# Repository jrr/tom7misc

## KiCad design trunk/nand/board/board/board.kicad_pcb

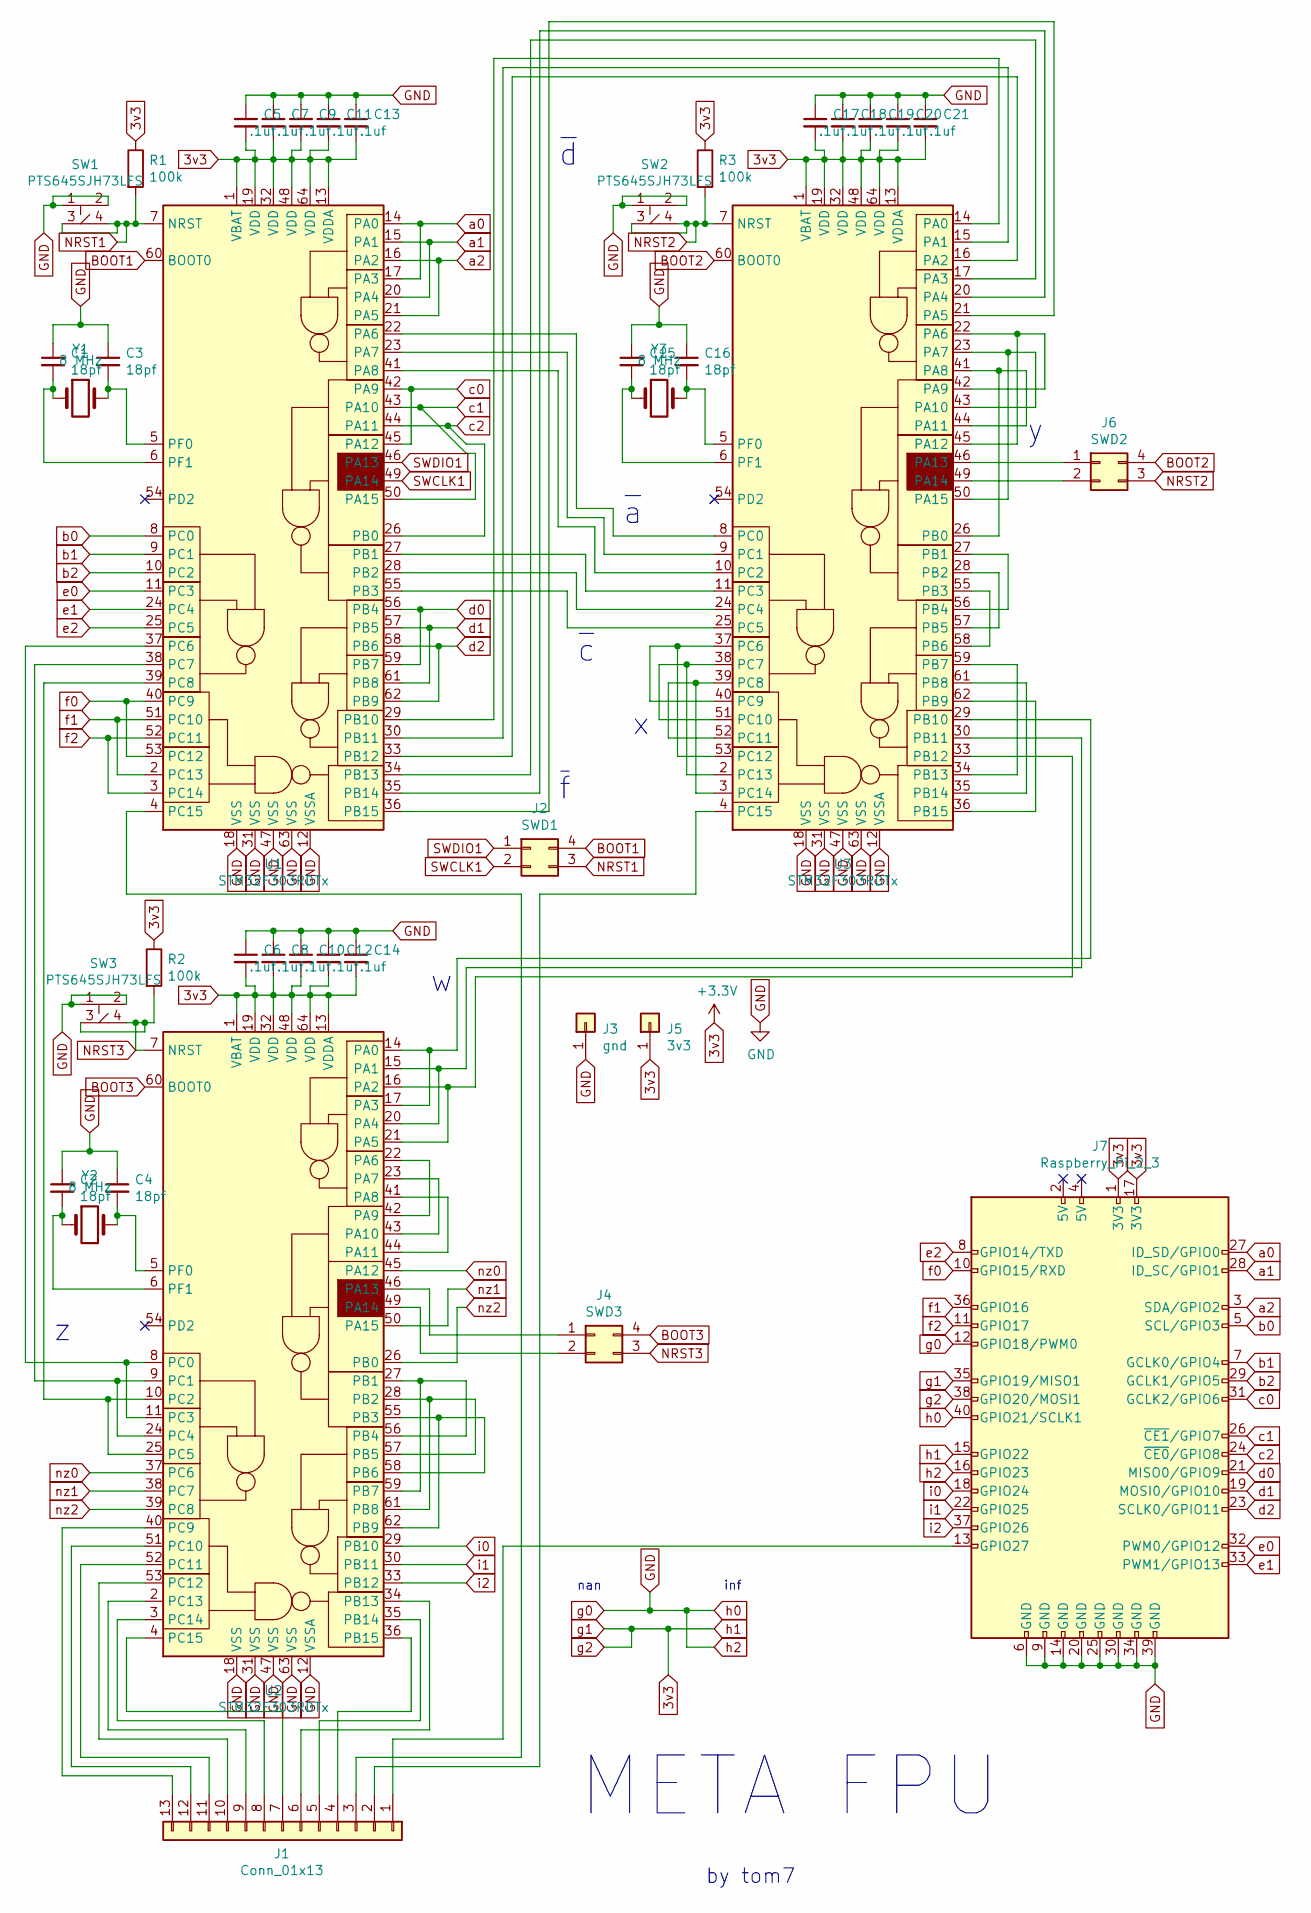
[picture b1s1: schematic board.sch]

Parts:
C1, C2, C3, C4, C15, C16: 18pf; C_Disc_D6.0mm_W2.5mm_P5.00mm
C5, C6, C7, C8, C9, C10, C11, C12, C13, C14, C17, C18, C19, C20, C21: .1uf; C_Disc_D6.0mm_W2.5mm_P5.00mm
J1: Conn_01x13; PinHeader_1x13_P2.54mm_Vertical
J2: SWD1; PinHeader_2x02_P2.54mm_Vertical
J3: gnd; PinHeader_1x01_P2.54mm_Vertical
J4: SWD3; PinHeader_2x02_P2.54mm_Vertical
J5: 3v3; PinHeader_1x01_P2.54mm_Vertical
J6: SWD2; PinHeader_2x02_P2.54mm_Vertical
J7: Raspberry_Pi_2_3; PinHeader_2x20_P2.54mm_Vertical
R1, R2, R3: 100k; R_Axial_DIN0207_L6.3mm_D2.5mm_P7.62mm_Horizontal
SW1, SW2, SW3: PTS645SJH73LFS; PTS645SJH73LFS_FP
U1, U2, U3: STM32F303RDTx; LQFP-64_10x10mm_P0.5mm
Y1, Y2, Y3: 8 MHz; Crystal_HC49-U_Vertical

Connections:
3v3: C5.2, C6.2, C7.2, C8.2, C9.2, C10.2, C11.2, C12.2, C13.2, C14.2, C17.2, C18.2, C19.2, C20.2, C21.2, J5.1, J7.1 (3V3), J7.15 (GPIO22), J7.17 (3V3), J7.35 (GPIO19/MISO1), J7.38 (GPIO20/MOSI1), R1.1, R2.1, R3.1, U1.1 (VBAT), U1.13 (VDDA), U1.19 (VDD), U1.32 (VDD), U1.48 (VDD), U1.64 (VDD), U2.1 (VBAT), U2.13 (VDDA), U2.19 (VDD), U2.32 (VDD), U2.48 (VDD), U2.64 (VDD), U3.1 (VBAT), U3.13 (VDDA), U3.19 (VDD), U3.32 (VDD), U3.48 (VDD), U3.64 (VDD)
BOOT1: J2.4, U1.60 (BOOT0)
BOOT2: J6.4, U3.60 (BOOT0)
BOOT3: J4.4, U2.60 (BOOT0)
GND: C1.1, C2.1, C3.1, C4.1, C5.1, C6.1, C7.1, C8.1, C9.1, C10.1, C11.1, C12.1, C13.1, C14.1, C15.1, C16.1, C17.1, C18.1, C19.1, C20.1, C21.1, J3.1, J7.6 (GND), J7.9 (GND), J7.12 (GPIO18/PWM0), J7.14 (GND), J7.16 (GPIO23), J7.20 (GND), J7.25 (GND), J7.30 (GND), J7.34 (GND), J7.39 (GND), J7.40 (GPIO21/SCLK1), SW1.1, SW1.2, SW2.1, SW2.2, SW3.1, SW3.2, U1.12 (VSSA), U1.18 (VSS), U1.31 (VSS), U1.47 (VSS), U1.63 (VSS), U2.12 (VSSA), U2.18 (VSS), U2.31 (VSS), U2.47 (VSS), U2.63 (VSS), U3.12 (VSSA), U3.18 (VSS), U3.31 (VSS), U3.47 (VSS), U3.63 (VSS)
NRST1: J2.3, R1.2, SW1.3, SW1.4, U1.7 (NRST)
NRST2: J6.3, R3.2, SW2.3, SW2.4, U3.7 (NRST)
NRST3: J4.3, R2.2, SW3.3, SW3.4, U2.7 (NRST)
unnamed: C1.2, U1.6 (PF1), Y1.1
unnamed: C2.2, U2.6 (PF1), Y2.1
unnamed: C3.2, U1.5 (PF0), Y1.2
unnamed: C4.2, U2.5 (PF0), Y2.2
unnamed: C15.2, U3.6 (PF1), Y3.1
unnamed: C16.2, U3.5 (PF0), Y3.2
unnamed: J1.1, J7.13 (GPIO27)
unnamed: J1.2, U3.4 (PC15)
unnamed: J1.3, U1.4 (PC15)
unnamed: J1.4, U2.36 (PB15)
unnamed: J1.5, U2.35 (PB14)
unnamed: J1.6, U2.34 (PB13)
unnamed: J1.7, U2.4 (PC15)
unnamed: J1.8, U2.3 (PC14)
unnamed: J1.9, U2.2 (PC13)
unnamed: J1.10, U2.53 (PC12)
unnamed: J1.11, U2.52 (PC11)
unnamed: J1.12, U2.51 (PC10)
unnamed: J1.13, U2.40 (PC9)
unnamed: J4.1, U2.46 (PA13)
unnamed: J4.2, U2.49 (PA14)
unnamed: J6.1, U3.46 (PA13)
unnamed: J6.2, U3.49 (PA14)
unnamed: U1.22 (PA6), U3.8 (PC0)
unnamed: U1.23 (PA7), U3.9 (PC1)
unnamed: U1.27 (PB1), U3.11 (PC3)
unnamed: U1.28 (PB2), U3.24 (PC4)
unnamed: U1.29 (PB10), U3.14 (PA0)
unnamed: U1.30 (PB11), U3.15 (PA1)
unnamed: U1.33 (PB12), U3.16 (PA2)
unnamed: U1.34 (PB13), U3.17 (PA3)
unnamed: U1.35 (PB14), U3.20 (PA4)
unnamed: U1.36 (PB15), U3.21 (PA5)
unnamed: U1.37 (PC6), U2.8 (PC0), U2.11 (PC3)
unnamed: U1.38 (PC7), U2.9 (PC1), U2.24 (PC4)
unnamed: U1.39 (PC8), U2.10 (PC2), U2.25 (PC5)
unnamed: U1.41 (PA8), U3.10 (PC2)
unnamed: U1.55 (PB3), U3.25 (PC5)
unnamed: U2.14 (PA0), U2.17 (PA3), U3.29 (PB10)
unnamed: U2.15 (PA1), U2.20 (PA4), U3.30 (PB11)
unnamed: U2.16 (PA2), U2.21 (PA5), U3.33 (PB12)
unnamed: U2.22 (PA6), U2.42 (PA9)
unnamed: U2.23 (PA7), U2.43 (PA10)
unnamed: U2.27 (PB1), U2.56 (PB4), U2.59 (PB7)
unnamed: U2.28 (PB2), U2.57 (PB5), U2.61 (PB8)
unnamed: U2.41 (PA8), U2.44 (PA11)
unnamed: U2.55 (PB3), U2.58 (PB6), U2.62 (PB9)
unnamed: U3.2 (PC13), U3.38 (PC7), U3.51 (PC10)
unnamed: U3.3 (PC14), U3.39 (PC8), U3.52 (PC11)
unnamed: U3.22 (PA6), U3.42 (PA9), U3.45 (PA12)
unnamed: U3.23 (PA7), U3.43 (PA10), U3.50 (PA15)
unnamed: U3.26 (PB0), U3.41 (PA8), U3.44 (PA11)
unnamed: U3.27 (PB1), U3.56 (PB4)
unnamed: U3.28 (PB2), U3.57 (PB5)
unnamed: U3.34 (PB13), U3.59 (PB7)
unnamed: U3.35 (PB14), U3.61 (PB8)
unnamed: U3.36 (PB15), U3.62 (PB9)
unnamed: U3.37 (PC6), U3.40 (PC9), U3.53 (PC12)
unnamed: U3.55 (PB3), U3.58 (PB6)
SWCLK1: J2.2, U1.49 (PA14)
SWDIO1: J2.1, U1.46 (PA13)
a0: J7.27 (ID_SD/GPIO0), U1.14 (PA0), U1.17 (PA3)
a1: J7.28 (ID_SC/GPIO1), U1.15 (PA1), U1.20 (PA4)
a2: J7.3 (SDA/GPIO2), U1.16 (PA2), U1.21 (PA5)
b0: J7.5 (SCL/GPIO3), U1.8 (PC0)
b1: J7.7 (GCLK0/GPIO4), U1.9 (PC1)
b2: J7.29 (GCLK1/GPIO5), U1.10 (PC2)
c0: J7.31 (GCLK2/GPIO6), U1.42 (PA9), U1.45 (PA12)
c1: J7.26 (~CE1~/GPIO7), U1.43 (PA10), U1.50 (PA15)
c2: J7.24 (~CE0~/GPIO8), U1.26 (PB0), U1.44 (PA11)
d0: J7.21 (MISO0/GPIO9), U1.56 (PB4), U1.59 (PB7)
d1: J7.19 (MOSI0/GPIO10), U1.57 (PB5), U1.61 (PB8)
d2: J7.23 (SCLK0/GPIO11), U1.58 (PB6), U1.62 (PB9)
e0: J7.32 (PWM0/GPIO12), U1.11 (PC3)
e1: J7.33 (PWM1/GPIO13), U1.24 (PC4)
e2: J7.8 (GPIO14/TXD), U1.25 (PC5)
f0: J7.10 (GPIO15/RXD), U1.40 (PC9), U1.53 (PC12)
f1: J7.36 (GPIO16), U1.2 (PC13), U1.51 (PC10)
f2: J7.11 (GPIO17), U1.3 (PC14), U1.52 (PC11)
i0: J7.18 (GPIO24), U2.29 (PB10)
i1: J7.22 (GPIO25), U2.30 (PB11)
i2: J7.37 (GPIO26), U2.33 (PB12)
nz0: U2.37 (PC6), U2.45 (PA12)
nz1: U2.38 (PC7), U2.50 (PA15)
nz2: U2.26 (PB0), U2.39 (PC8)

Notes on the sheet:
META FPU
by tom7
nan
inf

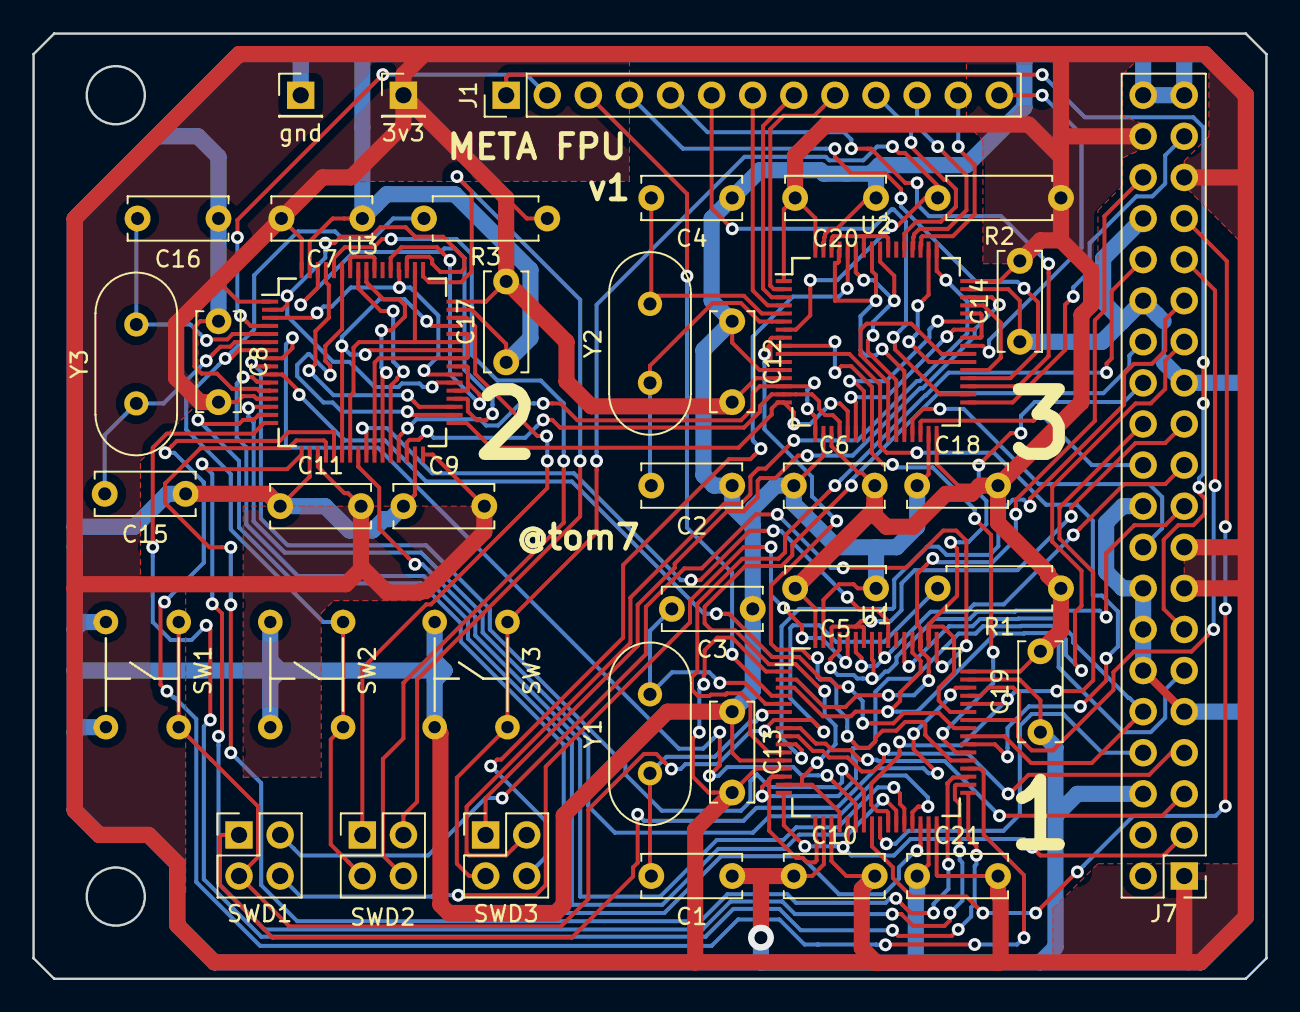
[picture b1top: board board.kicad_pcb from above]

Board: 2 copper layers, 76.2 x 58.4 mm, 40 parts (0 on the bottom side), 93 nets.

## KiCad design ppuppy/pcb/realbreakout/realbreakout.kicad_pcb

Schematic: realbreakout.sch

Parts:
.1uf1, .1uf2, .1uf3: C; C_Disc_D5.0mm_W2.5mm_P5.00mm
E1: GLS29EE010; DIP-32_W15.24mm
J1, J2, J3: Conn_01x36; Pin_Header_Straight_1x36_Pitch2.54mm
J4: BCM25; Pin_Header_Straight_1x01_Pitch2.54mm
J5: BCM24; Pin_Header_Straight_1x01_Pitch2.54mm
J6: BCM27; Pin_Header_Straight_1x01_Pitch2.54mm
J7: 3V; Pin_Header_Straight_1x01_Pitch2.54mm
J8: GND; Pin_Header_Straight_1x01_Pitch2.54mm
J9: BCM10; Pin_Header_Straight_1x01_Pitch2.54mm
J10: BCM11; Pin_Header_Straight_1x01_Pitch2.54mm
J11: BCM13; Pin_Header_Straight_1x01_Pitch2.54mm
J12: /OE; Pin_Header_Straight_1x01_Pitch2.54mm
U1: nescartheader; cartedge
U2: piheader; Pin_Header_Straight_2x20_Pitch2.54mm
U3: nescic; DIP-16_W7.62mm
U4: CD74FCT245; DIP-20_W7.62mm
U5, U6: MC74VHCT50A; SOIC-14_3.9x8.7mm_Pitch1.27mm

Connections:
3v: .1uf2.2, .1uf3.2, J7.1, U2.1 (3v3), U2.17 (3v3), U5.14 (VCC), U6.14 (VCC)
3vA0: U2.8 (BCM14_TXD), U6.2 (Y1)
3vA1: U2.10 (BCM15_RXD), U6.4 (Y2)
3vA2: U2.36 (BCM16), U6.6 (Y3)
3vA3: U2.11 (BCM17), U6.8 (Y4)
3vA4: U2.12 (BCM18_PWM0), U6.10 (Y5)
3vA5: U2.35 (BCM19_MISO), U6.12 (Y6)
3vA6: U2.38 (BCM20_MOSI), U5.2 (Y1)
3vA7: U2.40 (BCM21_SCLK), U5.4 (Y2)
3vA8: U2.15 (BCM22), U5.6 (Y3)
3vA9: U2.16 (BCM23), U5.8 (Y4)
3vA13: U2.37 (BCM26), U5.10 (Y5)
3vRD: J12.1, U2.32 (BCM12_PWM0), U4.19 (/OE), U5.12 (Y6)
/5vRD: J1.21, U1.21 (/PPU_RD), U5.13 (A6)
/ROMSEL: E1.24 (/OE), J2.23, J3.23, U1.50 (/ROMSEL)
unnamed: E1.4 (A12), J2.34, J3.34, U1.39 (CPU_A12)
unnamed: E1.5 (A7), J1.6, U1.6 (CPU_A7)
unnamed: E1.6 (A6), J1.7, U1.7 (CPU_A6)
unnamed: E1.7 (A5), J1.8, U1.8 (CPU_A5)
unnamed: E1.8 (A4), J1.9, U1.9 (CPU_A4)
unnamed: E1.9 (A3), J1.10, U1.10 (CPU_A3)
unnamed: E1.10 (A2), J1.11, U1.11 (CPU_A2)
unnamed: E1.11 (A1), J1.12, U1.12 (CPU_A1)
unnamed: E1.12 (A0), J1.13, U1.13 (CPU_A0)
unnamed: E1.13 (D0), J2.24, J3.24, U1.49 (CPU_D0)
unnamed: E1.14 (D1), J2.25, J3.25, U1.48 (CPU_D1)
unnamed: E1.15 (D2), J2.26, J3.26, U1.47 (CPU_D2)
unnamed: E1.17 (D3), J2.27, J3.27, U1.46 (CPU_D3)
unnamed: E1.18 (D4), J2.28, J3.28, U1.45 (CPU_D4)
unnamed: E1.19 (D5), J2.29, J3.29, U1.44 (CPU_D5)
unnamed: E1.20 (D6), J2.30, J3.30, U1.43 (CPU_D6)
unnamed: E1.21 (D7), J2.31, J3.31, U1.42 (CPU_D7)
unnamed: E1.23 (A10), J1.3, U1.3 (CPU_A10)
unnamed: E1.25 (A11), J1.2, U1.2 (CPU_A11)
unnamed: E1.26 (A9), J1.4, U1.4 (CPU_A9)
unnamed: E1.27 (A8), J1.5, U1.5 (CPU_A8)
unnamed: E1.28 (A13), J2.33, J3.33, U1.40 (CPU_A13)
unnamed: E1.29 (A14), J2.32, J3.32, U1.41 (CPU_A14)
unnamed: J1.14, U1.14 (CPU_R/W)
unnamed: J1.15, U1.15 (/IRQ)
unnamed: J1.16, U1.16 (EXP_0)
unnamed: J1.17, U1.17 (EXP_1)
unnamed: J1.18, U1.18 (EXP_2)
unnamed: J1.19, U1.19 (EXP_3)
unnamed: J1.20, U1.20 (EXP_4)
unnamed: J1.22, U1.22 (CIRAM_A10)
unnamed: J1.23, U1.23 (PPU_A6), U5.1 (A1)
unnamed: J1.24, U1.24 (PPU_A5), U6.13 (A6)
unnamed: J1.25, U1.25 (PPU_A4), U6.11 (A5)
unnamed: J1.26, U1.26 (PPU_A3), U6.9 (A4)
unnamed: J1.27, U1.27 (PPU_A2), U6.5 (A3)
unnamed: J1.28, U1.28 (PPU_A1), U6.3 (A2)
unnamed: J1.29, U1.29 (PPU_A0), U6.1 (A1)
unnamed: J1.30, U1.30 (PPU_D0), U4.9 (A8)
unnamed: J1.31, U1.31 (PPU_D1), U4.8 (A7)
unnamed: J1.32, U1.32 (PPU_D2), U4.7 (A6)
unnamed: J1.33, U1.33 (PPU_D3), U4.6 (A5)
unnamed: J1.34, U1.34 (CIC_toPak), U3.2 (DATA_IN)
unnamed: J1.35, U1.35 (CIC_toMB), U3.1 (DATA_OUT)
unnamed: J2.2, J3.2, U1.71 (CIC_CLK), U3.6 (CLK)
unnamed: J2.3, J3.3, U1.70 (/CIC_RST), U3.7 (RESET)
unnamed: J2.4, J3.4, U1.69 (PPU_D4), U4.5 (A4)
unnamed: J2.5, J3.5, U1.68 (PPU_D5), U4.4 (A3)
unnamed: J2.6, J3.6, U1.67 (PPU_D6), U4.3 (A2)
unnamed: J2.7, J3.7, U1.66 (PPU_D7), U4.2 (A1)
unnamed: J2.8, J3.8, U1.65 (PPU_A13), U5.11 (A5)
unnamed: J2.9, J3.9, U1.64 (PPU_A12)
unnamed: J2.10, J3.10, U1.63 (PPU_A10)
unnamed: J2.11, J3.11, U1.62 (PPU_A11)
unnamed: J2.12, J3.12, U1.61 (PPU_A9), U5.9 (A4)
unnamed: J2.13, J3.13, U1.60 (PPU_A8), U5.5 (A3)
unnamed: J2.14, J3.14, U1.59 (PPU_A7), U5.3 (A2)
unnamed: J2.15, J3.15, U1.58 (/PPU_A13)
unnamed: J2.17, J3.17, U1.56 (/PPU_WR)
unnamed: J2.18, J3.18, U1.55 (EXP_5)
unnamed: J2.19, J3.19, U1.54 (EXP_6)
unnamed: J2.20, J3.20, U1.53 (EXP_7)
unnamed: J2.21, J3.21, U1.52 (EXP_8)
unnamed: J2.22, J3.22, U1.51 (EXP_9)
unnamed: J2.35, J3.35, U1.38 (M2)
unnamed: J2.36, J3.36, U1.37 (SYS_CLK)
unnamed: J4.1, U2.22 (BCM25)
unnamed: J5.1, U2.18 (BCM24)
unnamed: J6.1, U2.13 (BCM27)
unnamed: J9.1, U2.19 (BCM10_MOSI)
unnamed: J10.1, U2.23 (BCM11_SCLK)
unnamed: J11.1, U2.33 (BCM13_PWM1)
unnamed: U2.3 (BCM2), U4.18 (B1)
unnamed: U2.5 (BCM3_SCL), U4.17 (B2)
unnamed: U2.7 (BCM4_CLK0), U4.16 (B3)
unnamed: U2.21 (BCM9_MISO), U4.11 (B8)
unnamed: U2.24 (BCM8_CE0), U4.12 (B7)
unnamed: U2.26 (BCM7_CE1), U4.13 (B6)
unnamed: U2.29 (BCM5), U4.15 (B4)
unnamed: U2.31 (BCM6), U4.14 (B5)

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
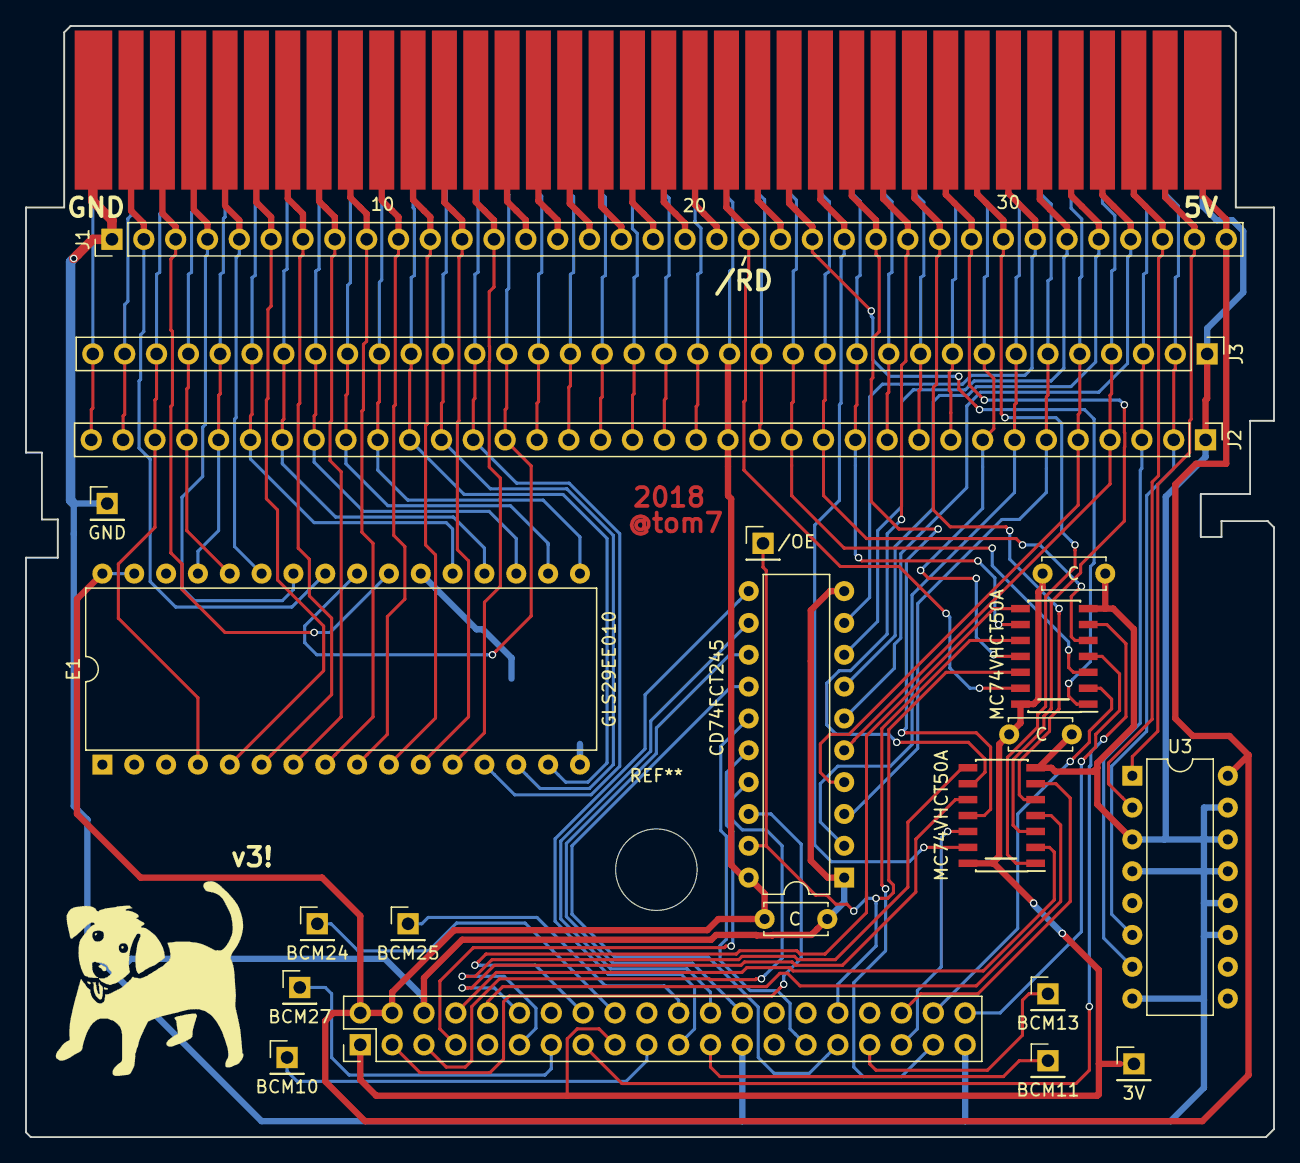
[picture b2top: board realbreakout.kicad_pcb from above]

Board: 2 copper layers, 99.6 x 88.6 mm, 22 parts (0 on the bottom side), 97 nets.

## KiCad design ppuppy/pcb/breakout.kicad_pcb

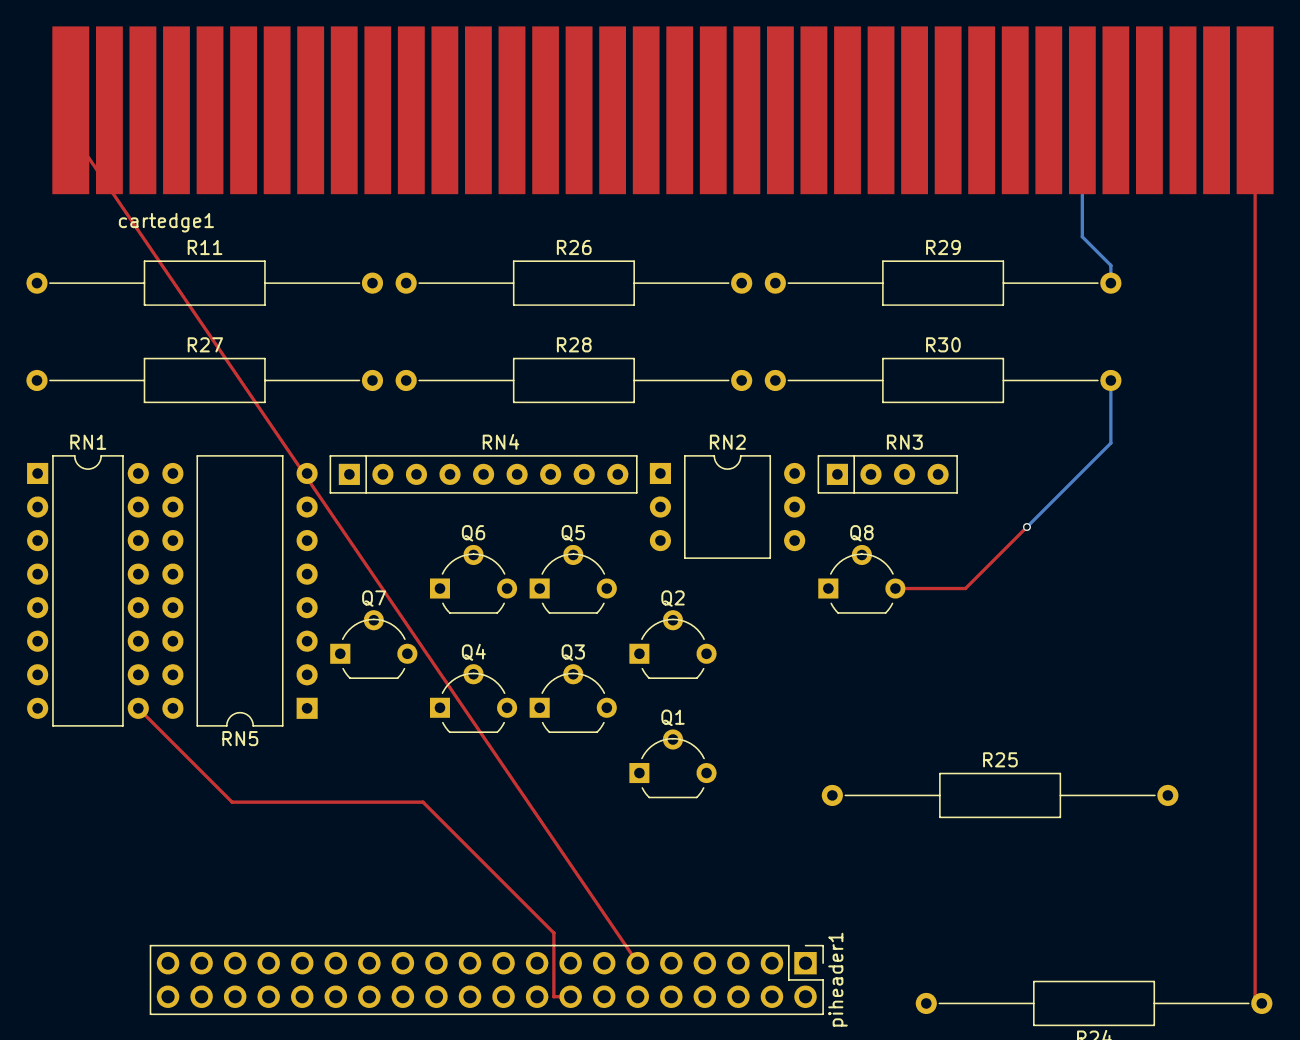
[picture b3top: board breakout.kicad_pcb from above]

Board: 2 copper layers, 23 parts (0 on the bottom side), 48 nets.

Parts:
Q1, Q2, Q3, Q4, Q5, Q6, Q7, Q8: 2N3904; TO-92_Molded_Wide
R11, R24, R25, R26, R27, R28, R29, R30: 4.7k; R_Axial_DIN0309_L9.0mm_D3.2mm_P25.40mm_Horizontal
RN1: 10k; DIP-16_W7.62mm
RN2: 1k; DIP-6_W10.16mm
RN3: 2k; R_Array_SIP4
RN4: 2k; R_Array_SIP9
RN5: 1k; DIP-16_W10.16mm
cartedge1: nescartheader; cartedge
piheader1: Raspberry_Pi_2_3; Pin_Header_Straight_2x20_Pitch2.54mm

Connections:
5V: R11.1, R24.1, R25.1, R26.1, R27.1, R28.1, R29.1, R30.1, cartedge1.36, piheader1.2
GND: Q1.1, Q2.1, Q3.1, Q4.1, Q5.1, Q6.1, Q7.1, Q8.1, RN3.1, RN4.1, cartedge1.1, cartedge1.72, piheader1.6
unnamed: Q1.2, RN1.8
unnamed: Q1.3, R11.2, cartedge1.30
unnamed: Q2.2, RN1.7
unnamed: Q2.3, R24.2, cartedge1.31
unnamed: Q3.2, RN1.6
unnamed: Q3.3, R25.2, cartedge1.32
unnamed: Q4.2, RN1.5
unnamed: Q4.3, R26.2, cartedge1.33
unnamed: Q5.2, RN1.4
unnamed: Q5.3, R27.2, cartedge1.69
unnamed: Q6.2, RN1.3
unnamed: Q6.3, R28.2, cartedge1.68
unnamed: Q7.2, RN1.2
unnamed: Q7.3, R29.2, cartedge1.67
unnamed: Q8.2, RN1.1
unnamed: Q8.3, R30.2, cartedge1.66
unnamed: RN1.9, piheader1.16
unnamed: RN1.10, piheader1.15
unnamed: RN1.11, piheader1.40
unnamed: RN1.12, piheader1.38
unnamed: RN1.13, piheader1.35
unnamed: RN1.14, piheader1.12
unnamed: RN1.15, piheader1.11
unnamed: RN1.16, piheader1.36
unnamed: RN2.1, RN3.4, piheader1.31
unnamed: RN2.2, RN3.3, piheader1.26
unnamed: RN2.3, RN3.2, piheader1.24
unnamed: RN2.4, cartedge1.61
unnamed: RN2.5, cartedge1.60
unnamed: RN2.6, cartedge1.59
unnamed: RN4.2, RN5.16, piheader1.18
unnamed: RN4.3, RN5.15, piheader1.22
unnamed: RN4.4, RN5.14, piheader1.37
unnamed: RN4.5, RN5.13, piheader1.13
unnamed: RN4.6, RN5.12, piheader1.3
unnamed: RN4.7, RN5.11, piheader1.5
unnamed: RN4.8, RN5.10, piheader1.7
unnamed: RN4.9, RN5.9, piheader1.29
unnamed: RN5.1, cartedge1.21
unnamed: RN5.2, cartedge1.23
unnamed: RN5.3, cartedge1.24
unnamed: RN5.4, cartedge1.25
unnamed: RN5.5, cartedge1.26
unnamed: RN5.6, cartedge1.27
unnamed: RN5.7, cartedge1.28
unnamed: RN5.8, cartedge1.29

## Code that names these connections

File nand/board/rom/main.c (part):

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  // 5 NAN gates:
  //
  //       x               y        ->       z
  // 0 (PA0,PA1,PA2) % (PA3,PA4,PA5) -> (PA6,PA7,PA8)
  // 1 (PA9,PA10,PA11) % (PA12,PA15,PB0) -> (PB1,PB2,PB3)
  // 2 (PB4,PB5,PB6) % (PB7,PB8,PB9) -> (PB10,PB11,PB12)
  // 3 (PC0,PC1,PC2) % (PC3,PC4,PC5) -> (PC6,PC7,PC8)
  // 4 (PC9,PC10,PC11) % (PC12,PC13,PC14) -> (PB13,PB14,PB15)
  //
  // Also configure PC15 as out. This is hooked to the header
  // and can send a signal for "i'm working".

  InitPinsIn(GPIOA,
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    ((READ1(in0, v0) << 2) | (READ1(in1, v1) << 1) | READ1(in2, v2))

  //       x               y        ->       z
  // 0 (PA0,PA1,PA2) % (PA3,PA4,PA5) -> (PA6,PA7,PA8)
  // 1 (PA9,PA10,PA11) % (PA12,PA15,PB0) -> (PB1,PB2,PB3)
  // 2 (PB4,PB5,PB6) % (PB7,PB8,PB9) -> (PB10,PB11,PB12)
  // 3 (PC0,PC1,PC2) % (PC3,PC4,PC5) -> (PC6,PC7,PC8)
  // 4 (PC9,PC10,PC11) % (PC12,PC13,PC14) -> (PB13,PB14,PB15)

    // pull out bits for xi, yi.
    const uint8_t x0 = READ3(inputa, 0, inputa, 1, inputa, 2);
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
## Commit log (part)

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2020-11-05 Standardize include guards, at least for source native to cc-lib. The __ prefix is actually reserved...
2020-11-07 Add stub drawing app, cloned from chess viewer
2020-11-07 Show FFT as you draw; inverse not yet built
2020-11-25 Various additions to image lib from DFX 2020 work
2020-11-27 Update stb_truetype. Add image blend to ImageRGBA
2020-11-27 Fork chess unblinder and make it compile here, but needs to be gutted
2020-11-27 Get this compiling without 'using namespace std' in headers
2020-11-28 Implement some TTF stuff based on stb_truetype, still loads of chess leftovers in here
2020-11-28 Normalize font, add icons
2020-11-29 sortition mode, but no actions yet
2020-12-06 Switch to normalized contours. Add start of code to detect fonts where the lowercase letters are just a scaled-down version of the uppercase.
2020-12-07 WriteLinesToFile utility. Do some error checking in util.cc that I should have done long ago
2020-12-07 Add bezier tesselation to lines utilities. Document some stuff in randutil. Make stb_truetype return failure code instead of asserting (seen in the wild)
2020-12-08 Test of auto-detecting fonts where uppercase and lowercase are the same
2020-12-10 Add some debugging stuff for aligning bitmaps
2020-12-10 Auto-alignment works. Black-box function optimization is kind of amazing??
2020-12-13 Version used to convert to font-db.txt format
2020-12-13 New version reads/writes fonts-db.txt. Add marking of samecase flag
2020-12-17 Improvements for sortition mode. Code to normalize lines as beziers
2020-12-18 Do a bit of cleanup to Network and add dense layer type (just advisory for now)
2020-12-18 Split out fontdb, start cleaning up training code, add 'cut deck' mode for cur_filenames
2020-12-18 loadpositions -> loadfonts
2020-12-19 Got train compiling. Move render style stuff to Network object. Initialize dense layers; no special training support yet. Make UI an object with local state. Add 'Top' for win32 builds (not yet used).
2020-12-20 Optimize some CL code, especially for dense layers. Makes it a little more complicated but +18% throughput is hard to argue with
2020-12-21 Don't send unused arguments. This doesn't seem to affect performance at all
2020-12-21 Add CPU implementation of Forward pass, not yet used
2020-12-22 Version that trained first-vectornet
2020-12-24 Smaller input/output size; seems to work better. Option to normalize points
2020-12-28 Some more uses of autoparallel, fix bugs there. Clean out verbose round from train.cc. Try a more forgiving loss function, but after a bunch of careful thought, realize that my approach to computing 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
2020-12-28 New heuristic version of this that's simpler and probably faster. Still untested though
2020-12-29 OK, this approach works fine for simple shapes. Added simple try-out mode in UI
2020-12-30 Add test for font-problem. In addition to being slow, it's pretty unstable. So I think this is probably just a bad approach.
2020-12-30 Ignore startx,starty when drawing. Assume a closed loop
2020-12-31 Add utilities ParseDouble and Factorize. Add simple bilinear filtering to ImageA, and Crop32. Some notes
2020-12-31 Load SDFs. sdf-info shows that these are good settings, usually falling off completely before the edge, and only dropping about 4% of fonts for not fitting in the box. Add scaled drawing to UI.
2021-01-01 More progress towards SDF and co-training; still not ready to go though
2021-01-01 All right, let's train these bad boys
2021-01-03 Somehow have achieved reasonable training. Added eval stuff like in vector version, switched to accessor methods for ImageA and ImageRGBA. Moved SDFConfig to FontProblem (a little more natural).
2021-01-03 Incompatible change to ImageRGBA and ImageA: Make the fields private (and non-const) so that I can add copy/assignment/move constructors.
2021-01-09 Add error history tracking
2021-01-10 modelinfo computes histograms of biases and weights in an image
2021-01-10 Split out modelinfo into lib and use it in train UI to diagnose runaway weights
2021-01-14 Much better decay factor, at least for this problem after 200k rounds. Long term eval export to spreadsheets
2021-01-16 Make compliation not require 'using namespace std' from some cc-lib header. Fix minor bug in unblinder found while working on lowercase
2021-01-18 Add 'widen' tool, which still has a bug
2021-01-18 Fix bug in widen
2021-01-19 Add [[noreturn]] attribute to this destructor so that LOG(FATAL) is accepted without warning in cases where the compiler would otherwise want us to return a value
2021-01-19 New 1D widening operation. Factored out EZLayer.
2021-01-24 Add line (segment) intersection test, ported from sml-lib
2021-01-24 Start on code to explicitly generate image features
2021-01-24 Add closest point to segment and distance to segment to lines.h
2021-01-24 indeed that was breaking 😳
2021-01-25 Makefeatures generates a suite of distant features, and widen can copy them from a network.
2021-01-27 Added new utility for deepening an existing network in place
2021-01-30 BlendBox and ScaleBy in image. Add rolling-average util (headr only). ParallelFan in threadutil
2021-02-06 Tweak some visualizations, like adding tick marks in histo code.
2021-02-07 Untabify everything... somehow this setting got lost when I upgraded emacs
2021-02-07 Possibly dead-end noodling trying to simplify the way this is called; commented-out
2021-02-07 Untabify everything (should be no other changes). Somehow my settings were lost when I upgraded emacs?
2021-02-07 Port db files to new aphasia2 syntax
2021-02-11 New option for bias in widen (might be bad idea). Additional computations in sdf-info. Move ttf code into ttf.cc and clean up a little
2021-02-12 Offline bitmap-based eval for one letter
2021-02-12 really simple improvement to SDFFromBitmap, but can do better
2021-02-12 Hah, actually it is substantially faster if you don't ignore the bound and remove the debugging assertino
2021-02-13 OK, this is 15x faster than the original, should be good enough for interactive use
2021-02-13 Live font drawing in ui, but needs guides etc.
2021-02-14 Add local port-scanning tool
2021-02-14 untabify tempo
2021-02-14 Tried implementing negative temperatures. Switched 'microdegs' to 'millidegs' everywhere (this was just wrong). Might not compile
2021-02-14 Improve graph aesthetics
2021-02-15 Try to find max activations for certain letters with search
2021-02-16 Tried doing >0 instead of EVEN_ODD but it turns out this is not easy with SDF. Probably not that interesting anyway
2021-02-16 Add direct bitmap 8x8 generation, which is about twice as fast as the naive conversion
2021-02-17 Untabify chess project and fix include guards
2021-02-17 Make tournament simulate deterministic matches for free
2021-02-17 Add silly letter-based player from lowercase project
2021-02-17 Fix another bug producing nondeterminism (and, wrong results) in letter-player
2021-02-17 misc style/standard fixes
2021-02-20 add float-based threshold/aa operation that does bilinear resize only once, and move to that. be clearer about scale vs quality params because I kept confusing myself. add crap prediction output in ui
2021-02-20 Implement gamma sliders for UI; seems useful
2021-02-21 Some notes and sketching in here, ready to clean up
2021-02-21 Clean up so it compiles again; output debug bitmap which looks OK
2021-02-27 Some initial work on auto-tracing; not working yet
2021-02-27 Did outstanding TODO to represent Contour as inherently closed
2021-03-03 Fix contour optimization... which was actually just a fairly shallow problem with ReverseContours!
2021-03-05 Add far superior (well, faster) algorithm for cubic bezier distance from Graphics Gems, not cleaned up. Also add initial port attempt in distance.cc, but just for posterity (it has some unknown bug).
2021-03-06 SDF font generation is working, yay
2021-03-06 Use ImageF in more places, since model does output floats and it does seem to improve the quality a little
2021-03-08 Multi font generation and tweaks. Add and start paper
2021-03-10 Some work on paper
2021-03-11 Generate font from vector version, write about this
2021-03-13 Just realized that I was writing about an older and much worse version of the vector net, ugh
2021-03-13 Fixed various bugs in my first attempt to use the old vector models. Generate new, much better fonts from the second version (duhhh). Update paper to tell this story
2021-03-16 Fix long-standing bug in BlendImage; how did I not run into that before?? Some miscellaneous improvements there, and to opt/ as well
2021-03-18 Add marching cubes wrapper with my debugging craps
2021-03-20 More work on paper, getting there...
2021-03-21 Wrote a bunch more...
2021-03-22 Paper almost done
2021-03-27 Breaking change: Avoid 'LoadImage' in sdlutil since windows.h redefines this sometimes. Some other small tweaks
2021-04-03 Try just including SDL_net in the source for escapex; it's pretty small and can maybe save me some linking/including headaches
2021-04-03 (and convert DOS line endings)
2021-04-03 Got this compiling again on my windows 10 desktop machine to test out solution uploading
2021-04-04 Cleanup/modernization. Move util to escape-util so it doesn't conflict with cc-lib's util, which is also linked/included. Got rid of some top-level stuff in escape-util, like stringlist pop stuff, wh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
2021-04-04 CopyImage for escape packpng
2021-04-04 Use Font from cc-lib/sdl, which originally came from escape anyway. Some more header cleanup and modernization.
2021-04-04 Rename Font::create, mostly to see what compileable projects still refer to this. Fix 'em. Some other miscellaneous small fixes throughout
2021-04-16 Consolidate graphics loading into a class that doesn't depend on SDL, so that I can make screenshot.exe headless. screenshot.exe is broken by this, though
2021-04-17 Add FromRGBA to convert from image.h format
2021-04-17 Basic headless screenshot, missing some fine touches
2021-04-17 More routines to support escapex screenshots
2021-04-17 Update screenshot path and provide hint for mystery I keep solving
2021-04-19 Further cleanup/modernization. Remove top-level 'itos'. Use vector instead of manually-managed linked-list for http/rpc (rip 'formalist'). Some include cleanup. Move implementation of client to .cc. 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
2021-04-21 Remove use of PtrList in Menu, and nearby modernization/cleanup. Fixed bug where downloading solutions from server did not write the player file. Don't generate animation_x.h files that aren't used a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
2021-04-24 Checkpoint before new approach
2021-04-25 Start implementing some basic tests, reminding myself how to use javascript :)
2021-04-30 Complete some of the implementation of Sim, fix some bugs, and add extremely basic tests. Enable strict typescript for this module at least.
2021-05-01 Add utility that randomly tests ops (mostly zip/zipStep properties), arcfour prng, test ops pass test
2021-05-01 Fix bug in arcfour, add function to advance consensus frame and test it
2021-05-02 Implement gamepad and interactive test
2021-05-03 move
2021-05-04 linux and windows CI
2021-05-04 fewer artifacts
2021-05-06 move some things
2021-05-07 moving things
2021-05-07 dockerized linux build env
2021-05-07 gitignore
2021-05-07 organizing
2021-05-07 link order
2021-05-07 one escobjects to rule them all
2021-05-07 remove apparently-unnecessary file
2021-05-07 remove stuff
2021-05-07 log gcc version
2021-05-07 gcc-8 on macos
2021-05-07 build cclib on mac
2021-05-07 sdlutil.a
2021-05-07 rearrange
2021-05-07 iterating on mac
2021-05-07 build screenshot.exe
2021-05-07 work around flaky apt source
2021-05-07 packsound
2021-05-08 packpng
2021-05-08 mkupgrade
2021-05-08 restore strip
2021-05-08 misc (#3)
    * move some things
    * detect OS
    * moving things
    * dockerized linux build env
    * esclib.a
    * gitignore
2021-05-08 matrix build
2021-05-08 common .o rule
2021-05-08 targets to the bottom
2021-05-08 More make (#5)
    * full ci mac build
    * matrix build
    * common .o rule
    * rearrange
    * cleanup
    * targets to the bottom
